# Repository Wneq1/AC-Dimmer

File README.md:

# AC-Dimmer

Power regulator for arduino 

In today's project, we will focus on building a power regulator using an Arduino microcontroller and a thyristor. Power regulators are commonly used to control the amount of electrical energy supplied to loads such as lamps, heaters, or motors, in order to adjust their brightness, temperature, or speed. By building your own power regulator using Arduino and a thyristor, you can create a cost-effective and customized solution for controlling AC loads in DIY projects or home automation systems. IF you wish to built one by yourselfe in this file, you can find a finished project in KiCad and short code in Arduino.

WARNING: THIS PROJECT INVOLVES HIGH VOLTAGES THAT CAN BE DANGEROUS TO LIFE AND HEALTH. 
YOU PERFORM THIS PROJECT AT YOUR OWN RISK AND RESPONSIBILITY.

To complete this project you will need:
Arduino or other microcontroller
* Fuse
* Resistors
    * 68k x2
    * 33k x2
    * 360 x1
    * 330 x2
    * 10k x5
    * 39 x1
* Capacitors
    * 0.01uF x1
    * 100nF x1
    * 25uF x1
* Optocoupler PC817
* Hi-link
* LM7805 (5V regulator)
* LED
* Optotriac MOC3041
* Pushbuttons
* OLED Display
* Thyristor BT138

Our system consists of several modules: 
* power module
* actuator module
* measurement module
* logic module

Short description of this project:

The power module is designed to deliver a stable 5V due to the current drawn by the circuit. I decided to use a pre-made Hi-Link power module, but if there is no need to support the interface (display buttons), a transformerless power supply can be used. The type of regulation used in the project is phase regulation. 
The disadvantage of this type of control is radio-electric interference, which appears when working with high-power receivers.

The measurement module consists of an optoelectronic component that is designed to detect the zero crossing of the input signal and then send information to the control module.

The output module consists of a triac that is turned on for a specified period by the microcontroller. In case the circuit needs to handle inductive loads, an additional capacitor and resistor should be added (refer to the datasheet).

The logic module consists of an Arduino microcontroller (or any other microcontroller that supports interrupts). The microcontroller operates based on interrupts (if zero crossing is detected, the microcontroller interrupts the currently running task and performs the interrupt function, i.e. turns on a timer that counts how long the output module should be turned on, and then turns off the triac).

Our device has 4 buttons, of which only 3 are used. One button is used to increase the power, the second to decrease it, and the third is the so-called "latch" button. There is also an LED used to indicate whether the latch is active. If the LED is on (button active), we can edit the power value by increasing or decreasing it. However, if the LED is off, we cannot edit the power value (even if we press other buttons, the power value will not change).

In AC-powered devices, power is closely related to the area under the sine wave applied to the input of our controlled system (e.g., a light bulb), and it is this area that can be regulated. However, in order to do this, we need a reference point. Since the signal present in the power socket is sinusoidal in nature, our reference point will be the zero crossing of the waveform, which will define how long our load will be energized. The longer the duration, the higher the power.

Now, let's do some math. Let's say the frequency of the power grid is 50 Hz, which means the period is f=1/T T=1/f=1/50=20[ms]. In each cycle, there are two peak values of the sine wave, so we reach the peak every 10 ms. If we manage to turn on the light bulb at the very beginning, it will receive 100% of the available power. If we turn it on halfway through (5 ms), it will receive 50% of the power, and if we turn it on towards the end of the 10 ms period, it will remain off (0% power).

Short description:

The blue waveform illustrates the mains voltage, while the orange waveform represents the response of the circuit to the previously applied power (response of the triac).
The waveform appearance for 100% power:

The waveform appearance for 50% power:

The waveform appearance for 25% power:

Below are some illustrative photos and link to video prezentation:

Short presentation on YouTube:
https://www.youtube.com/watch?v=zxgGnlvmVzU

In the files, you can also find another version of the Arduino code called 'Final Version,' where the only change is the selection mode of the controller values. However, the operating principle remains the same as in the previous version. You can find the link below.
Short presentation of Finall Version on YouTube:
https://www.youtube.com/watch?v=YGqYrHkOaR0

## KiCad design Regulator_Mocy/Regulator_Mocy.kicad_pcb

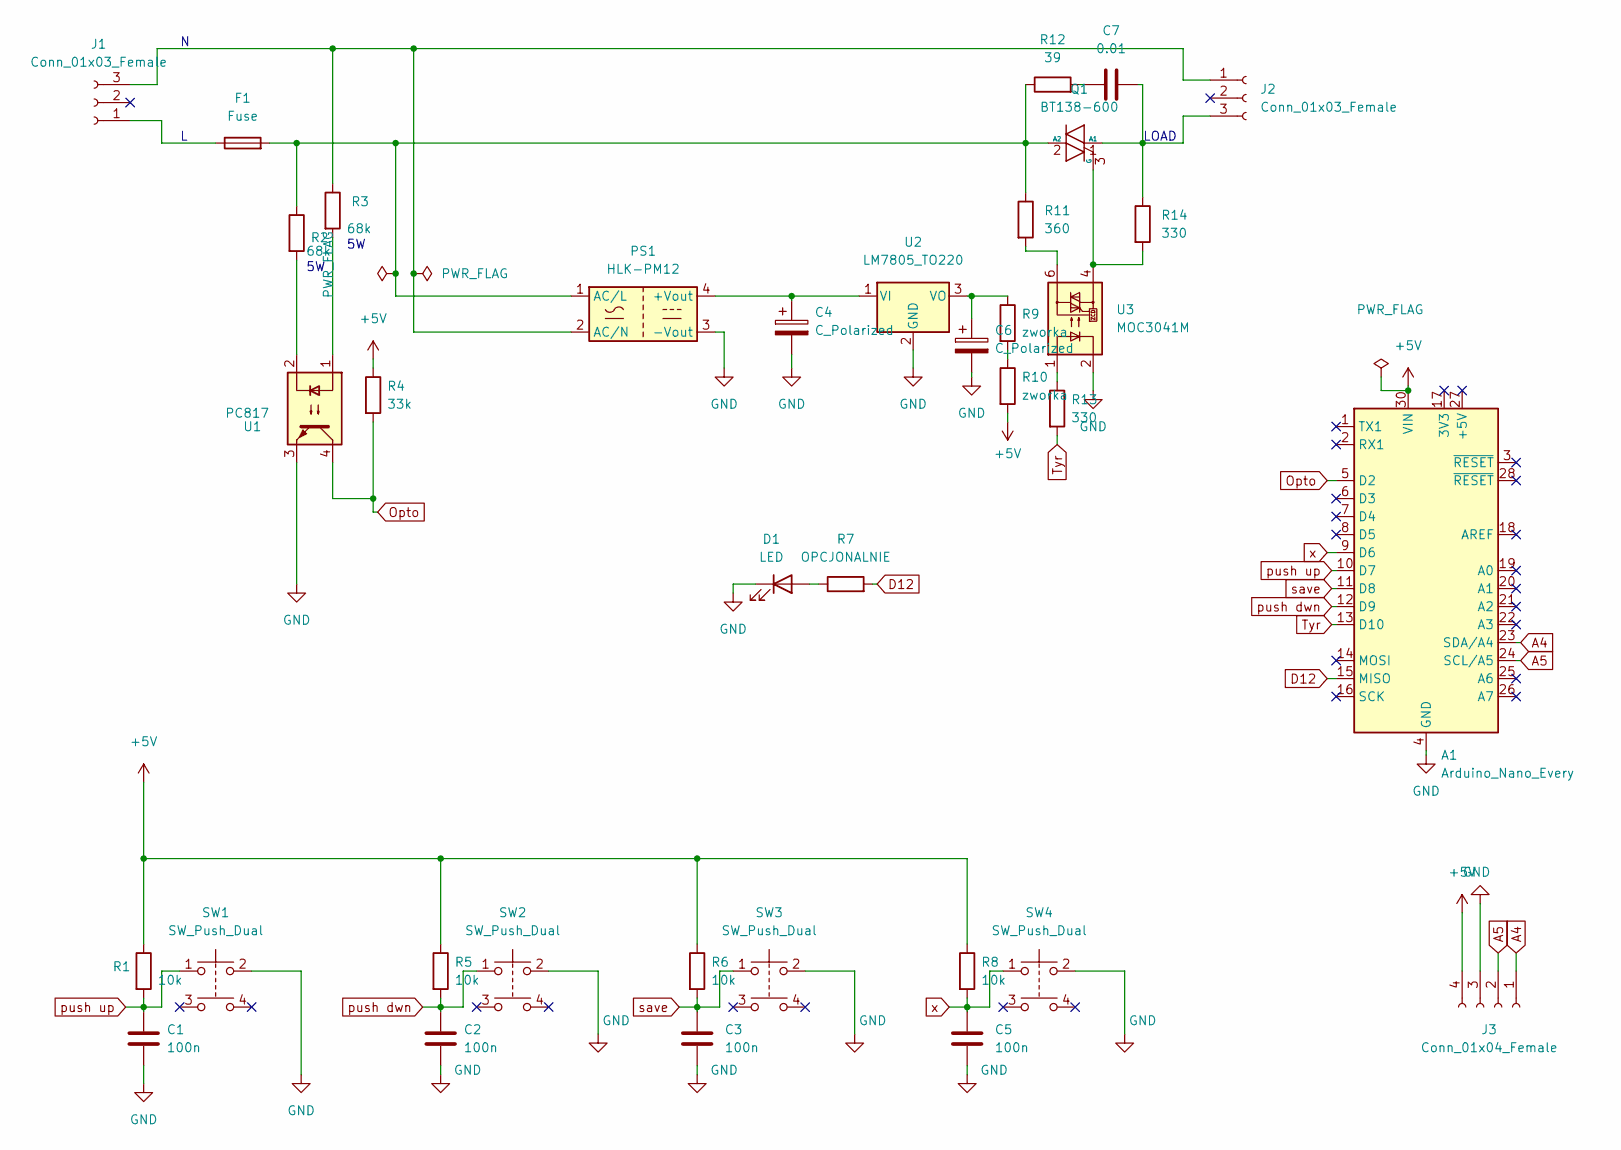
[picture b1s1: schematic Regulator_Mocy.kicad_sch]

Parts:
A1: Arduino_Nano_Every; Arduino_Nano
C1, C2, C3, C5: 100n; C_Axial_L3.8mm_D2.6mm_P10.00mm_Horizontal
C4, C6: C_Polarized; CP_Radial_D8.0mm_P3.80mm
C7: 0.01; C_Rect_L24.0mm_W10.1mm_P22.50mm_MKT
D1: LED; LED_D5.0mm
F1: Fuse; Fuseholder_Cylinder-5x20mm_Schurter_0031_8201_Horizontal_Op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
J1, J2: Conn_01x03_Female; Molex_KK-396_A-41792-0003_1x03_P3.96mm_Horizontal
J3: Conn_01x04_Female; PinHeader_1x04_P2.54mm_Vertical
PS1: HLK-PM12; Converter_ACDC_HiLink_HLK-PMxx
Q1: BT138-600; TO-220-3_Vertical
R1, R5, R6, R8: 10k; R_Axial_DIN0207_L6.3mm_D2.5mm_P10.16mm_Horizontal
R2, R3: 68k; R_Axial_Power_L25.0mm_W9.0mm_P27.94mm
R4: 33k; R_Axial_DIN0207_L6.3mm_D2.5mm_P10.16mm_Horizontal
R7: OPCJONALNIE; R_Axial_DIN0207_L6.3mm_D2.5mm_P10.16mm_Horizontal
R9, R10: zworka; R_Axial_DIN0204_L3.6mm_D1.6mm_P5.08mm_Vertical
R11: 360; R_Axial_DIN0207_L6.3mm_D2.5mm_P10.16mm_Horizontal
R12: 39; R_Axial_Power_L25.0mm_W9.0mm_P27.94mm
R13, R14: 330; R_Axial_DIN0207_L6.3mm_D2.5mm_P10.16mm_Horizontal
SW1, SW2, SW3, SW4: SW_Push_Dual; SW_PUSH_6mm_H7.3mm
U1: PC817; DIP-4_W7.62mm
U2: LM7805_TO220; TO-220-3_Vertical
U3: MOC3041M; DIP-6_W7.62mm

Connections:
+5V: A1.30 (VIN), J3.4, R1.1, R4.1, R5.1, R6.1, R8.1, R10.2
A4: A1.23 (SDA/A4), J3.1
A5: A1.24 (SCL/A5), J3.2
D12: A1.15 (MISO), R7.2
GND: A1.4 (GND), A1.29 (GND), C1.2, C2.2, C3.2, C4.2, C5.2, C6.2, D1.1 (K), J3.3, PS1.3 (-Vout), SW1.2, SW2.2, SW3.2, SW4.2, U1.3, U2.2 (GND), U3.2
unnamed: C4.1, PS1.4 (+Vout), U2.1 (VI)
unnamed: C6.1, R9.1, U2.3 (VO)
unnamed: C7.1, R12.2
unnamed: C7.2, J2.3, Q1.1 (A1), R14.1
unnamed: D1.2 (A), R7.1
unnamed: F1.1, J1.1
unnamed: F1.2, PS1.1 (AC/L), Q1.2 (A2), R2.1, R11.1, R12.1
unnamed: J1.3, J2.1, PS1.2 (AC/N), R3.1
unnamed: Q1.3 (G), R14.2, U3.4
unnamed: R2.2, U1.2
unnamed: R3.2, U1.1
unnamed: R9.2, R10.1
unnamed: R11.2, U3.6
unnamed: R13.1, U3.1
Opto: A1.5 (D2), R4.2, U1.4
Tyr: A1.13 (D10), R13.2
push dwn: A1.12 (D9), C2.1, R5.2, SW2.1
push up: A1.10 (D7), C1.1, R1.2, SW1.1
save: A1.11 (D8), C3.1, R6.2, SW3.1
x: A1.9 (D6), C5.1, R8.2, SW4.1

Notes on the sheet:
LOAD

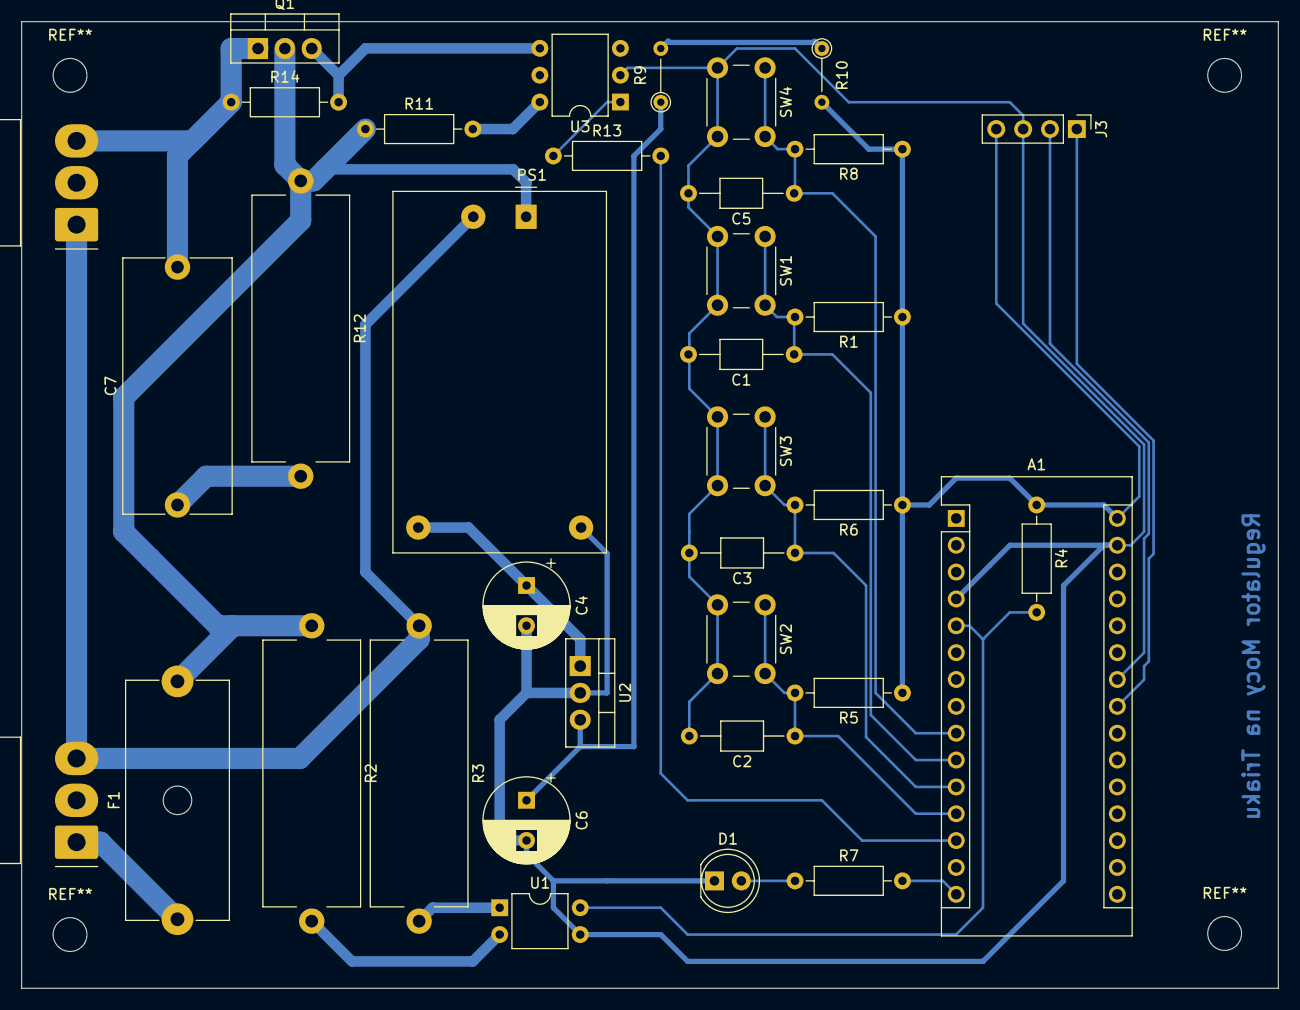
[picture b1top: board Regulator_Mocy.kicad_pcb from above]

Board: 2 copper layers, 118.9 x 91.4 mm, 36 parts (0 on the bottom side), 25 nets.

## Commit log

2023-05-19 Version V.2
2023-09-06 Create Phase_Regulator_EEPROM
2023-09-06 Create Group_Regulator
